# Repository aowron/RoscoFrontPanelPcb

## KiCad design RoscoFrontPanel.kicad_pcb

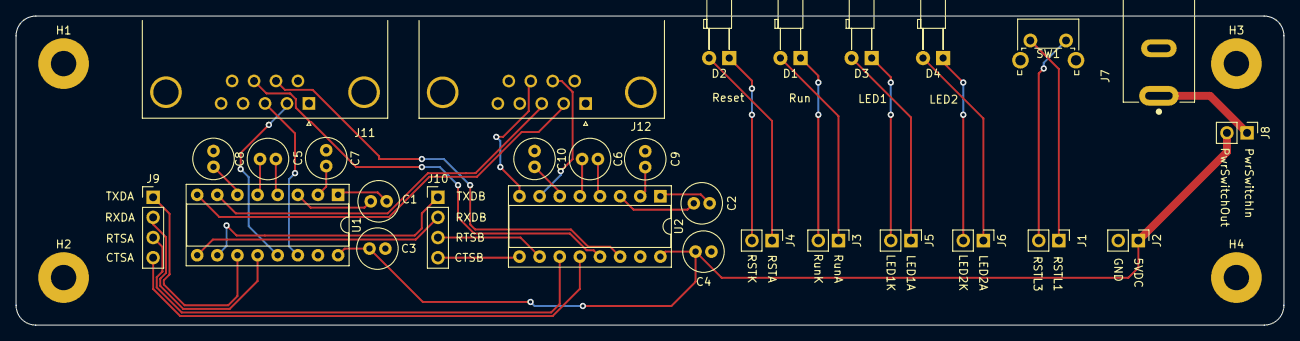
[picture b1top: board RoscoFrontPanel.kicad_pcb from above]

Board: 2 copper layers, 160.0 x 39.0 mm, 33 parts (0 on the bottom side), 41 nets.

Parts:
C1, C2, C3, C4, C5, C6, C7, C8, C9, C10: 1uF; C_Radial_D5.0mm_H11.0mm_P2.00mm
D1, D2, D3, D4: LED; LED_D3.0mm_Horizontal_O3.81mm_Z2.0mm
H1, H2, H3, H4: MountingHole; MountingHole_3.2mm_M3_Pad
J1, J2, J3, J4, J5, J6, J8: Conn_01x02_Male; PinHeader_1x02_P2.54mm_Vertical
J7: PJ-037B; CUI_PJ-037B
J9, J10: Conn_01x04_Male; PinHeader_1x04_P2.54mm_Vertical
J11, J12: DB9_Male; DSUB-9_Male_Horizontal_P2.77x2.84mm_EdgePinOffset7.70mm_Hou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
SW1: SW_DIP_x01; SW_Tactile_SPST_Angled_PTS645Vx83-2LFS
U1, U2: MAX232; DIP-16_W7.62mm_Socket

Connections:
+5V: C3.1, C4.1, J2.1, J8.2, U1.16, U2.16
/Led1A: D3.2, J5.1
/Led1K: D3.1, J5.2
/Led2A: D4.2, J6.1
/Led2K: D4.1, J6.2
/PwrSwitchIn: J7.1, J8.1
/RS232/CTSA: J9.4, U2.12
/RS232/CTSAOUT: J11.8, U2.13
/RS232/CTSB: J10.4, U2.9
/RS232/CTSBOUT: J12.8, U2.8
/RS232/RTSA: J9.3, U2.11
/RS232/RTSAOUT: J11.7, U2.14
/RS232/RTSB: J10.3, U2.10
/RS232/RTSBOUT: J12.7, U2.7
/RS232/RXDA: J9.2, U1.12
/RS232/RXDAOUT: J11.2, U1.13
/RS232/RXDB: J10.2, U1.9
/RS232/RXDBOUT: J12.2, U1.8
/RS232/TXDA: J9.1, U1.11
/RS232/TXDAOUT: J11.3, U1.14
/RS232/TXDB: J10.1, U1.10
/RS232/TXDBOUT: J12.3, U1.7
/ResetA: D2.2, J4.1
/ResetK: D2.1, J4.2
/ResetLeg1: J1.1, SW1.1
/ResetLeg3: J1.2, SW1.2
/RunA: D1.2, J3.1
/RunK: D1.1, J3.2
GND: C3.2, C4.2, C7.2, C8.1, C9.2, C10.1, J2.2, J7.2, J11.5, J12.5, U1.15, U2.15
unnamed: C1.1, U1.1
unnamed: C1.2, U1.3
unnamed: C2.1, U2.1
unnamed: C2.2, U2.3
unnamed: C5.1, U1.4
unnamed: C5.2, U1.5
unnamed: C6.1, U2.4
unnamed: C6.2, U2.5
unnamed: C7.1, U1.2
unnamed: C8.2, U1.6
unnamed: C9.1, U2.2
unnamed: C10.2, U2.6

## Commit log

2021-11-29 Minor design fixups
    * Added rounded corners
    * Rerouted tracks too close too pad
